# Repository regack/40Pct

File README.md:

The SmallFry 40% Board
=====

## v0.8-v0.10
* I forget everything that I did, lots of little things
* fixed some unconnected pads (oops)
* cleaned up silkscreens again
* fixed diode pads to fit SOD-123 footprint
* fixed BOM info for components
* rounded PCB edges
* replaced slotted holes with... holes
* added Vcc and Gnd pins to LED expansion
* changed LED expansion pins to 2.54 pitch

## v0.7 - 2013.10.20
* cleaned up silkscreens
* moved 'ROW5' expansion to GPIO7 (still ATMEGA32U4 pin8/PB0)
* added notes
* cleaned up and removed extra libs/mods

## v0.6 - 2013.10.16
* pulled extra pin for ROW5 from ATMEGA pin 8/PB0
* changed drills for holes/slots to work with OSHpark 
* added GPIO4, GPIO5, GPIO6 connectors to ATMEGA pins 26/PD6, 22/PD5, 11/PB3
* ran row and GPIO to 1.27mm headers on right-side of board for interconnect (ribbon cable spacing)

## v0.5 - 2013.09.20
* added back missing slot on right side of board
* added LEDs for optional keys from v0.4
* generated pcb image * not sure why slots don't render properly
* removed bottom-of-board expansion pins

## v0.4 - 2013.09.19
* added optional 1.25+1.0 and 1.0+1.25 for right-shift/fn keys

## v0.3 - 2013.09.18
* based on the GH60 Rev B PCB
* SMT ATMEGA32U4 and other components on back of board
* Expansion ports on bottom and top row
* LEDs on ESC, 'CAPS', and WASD Cluster
* Other LEDs in matrix with expansion points on top row

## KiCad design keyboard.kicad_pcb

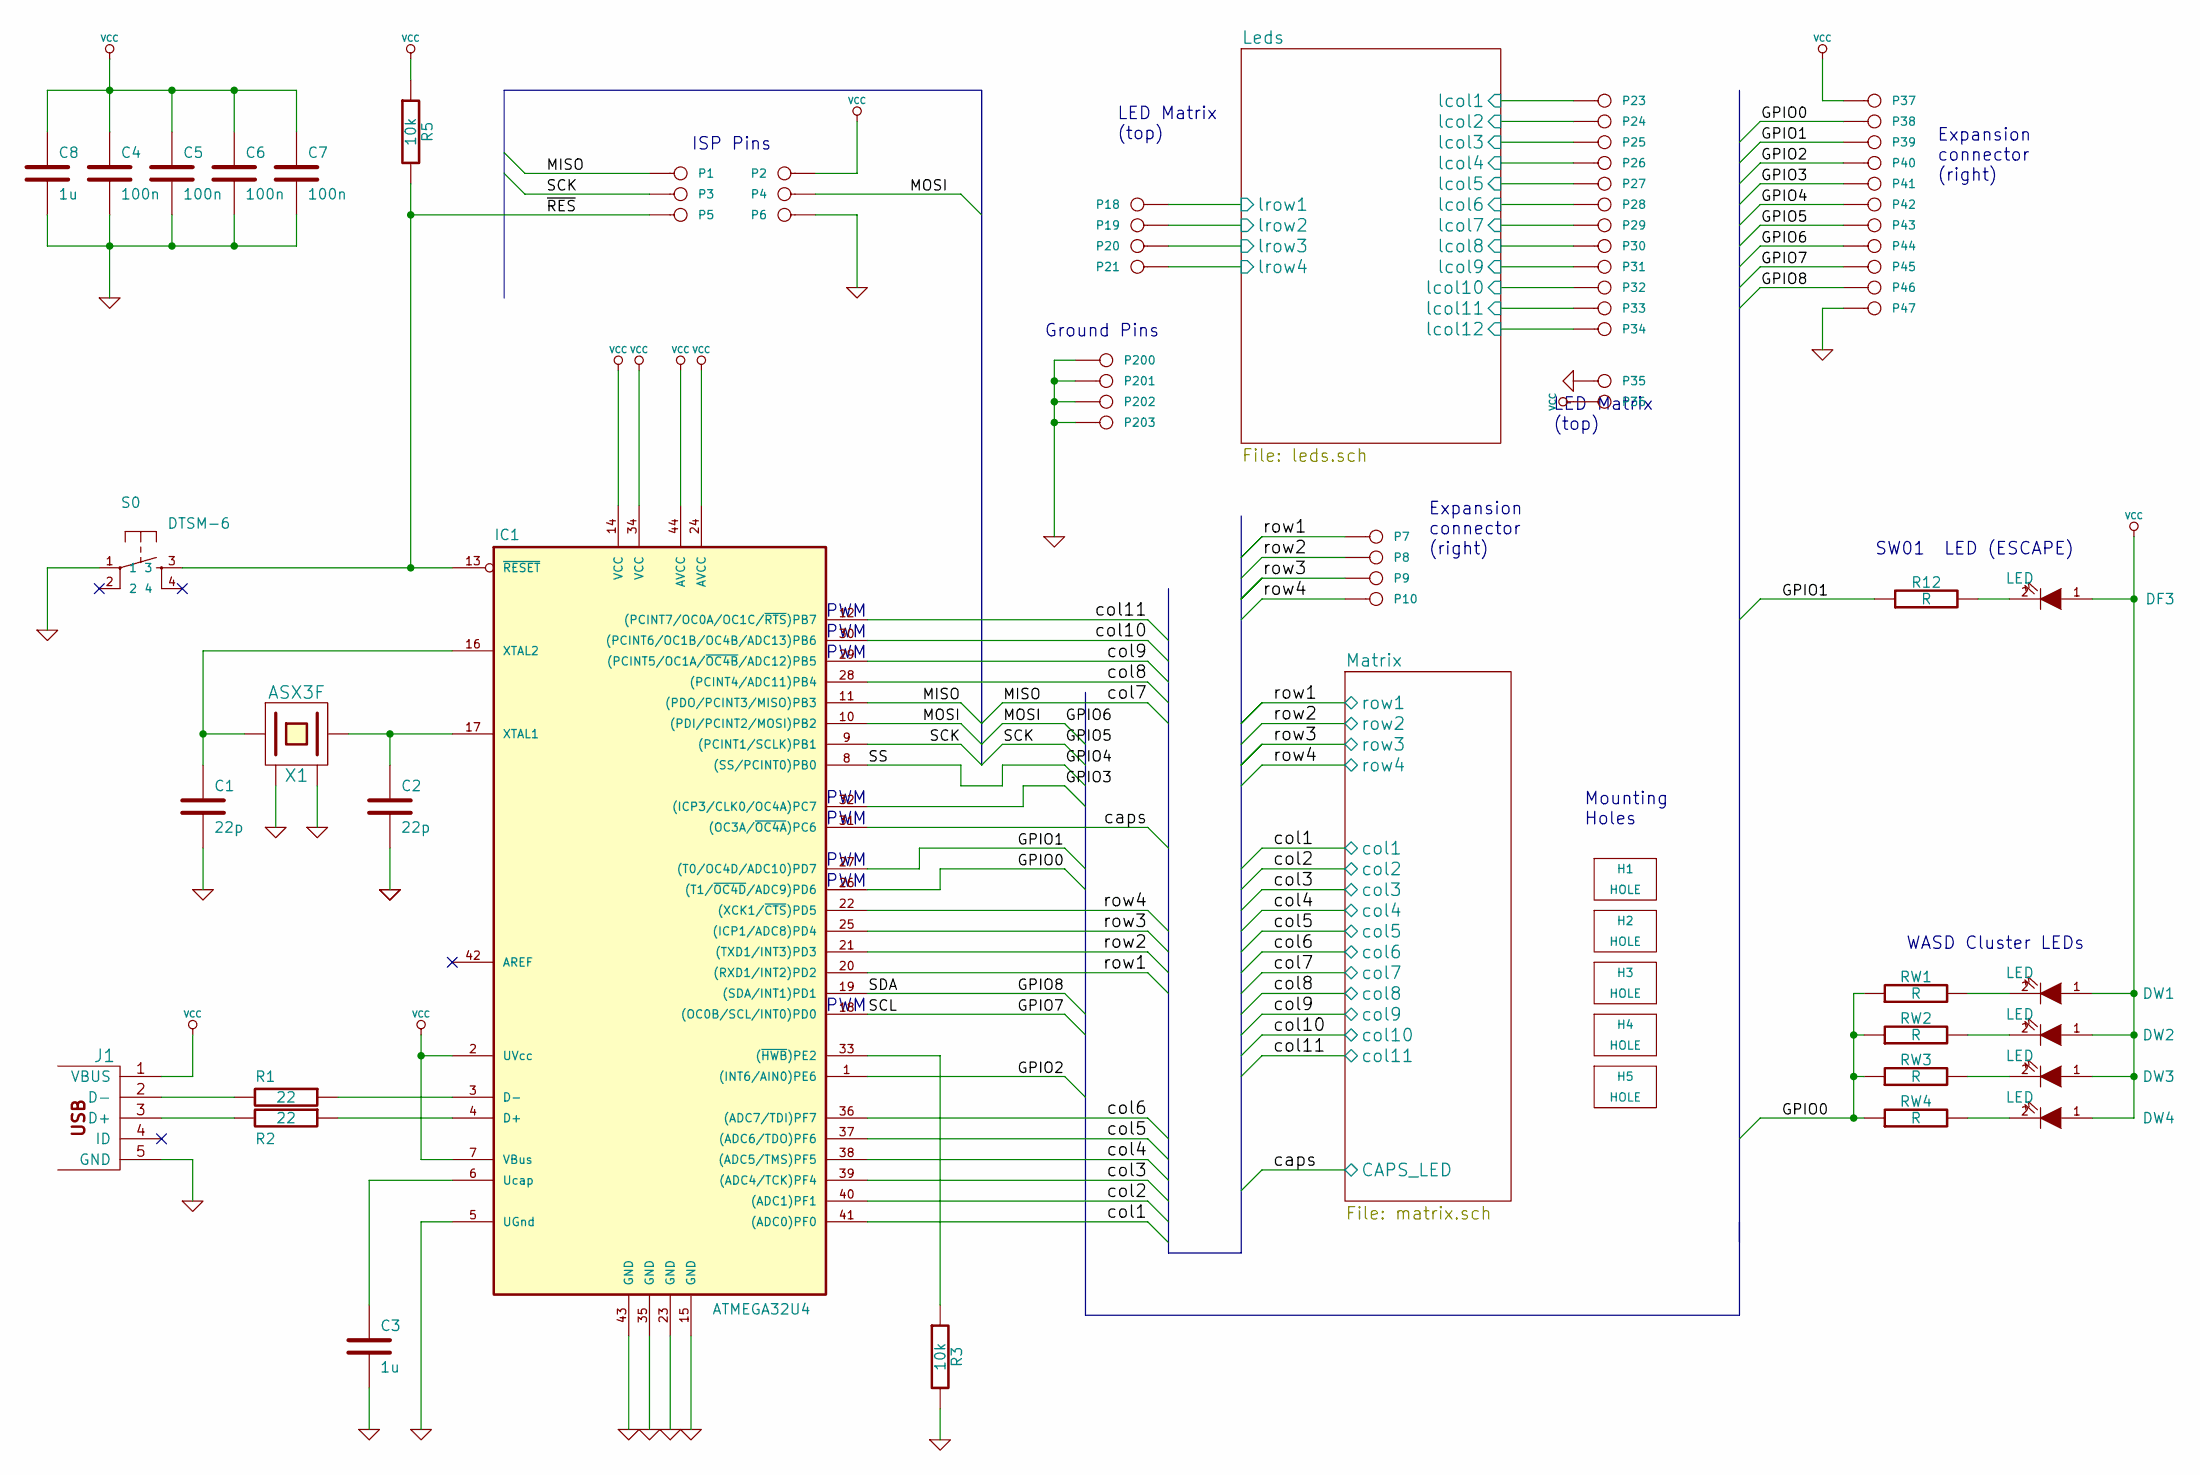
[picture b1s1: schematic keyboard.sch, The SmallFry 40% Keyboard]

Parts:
C1, C2: 22p
C3, C8: 1u
C4, C5, C6, C7: 100n
DF3: LED
DW1, DW2, DW3, DW4: LED
H1, H2, H3, H4, H5: HOLE
IC1: ATMEGA32U4; TQFP44
J1: MINI
P1: MISO
P2, P37: Vcc
P3: SCK
P4: MOSI
P5: RES
P6, P47, P200, P201, P202, P203: GND
P7: ROW1
P8: ROW2
P9: ROW3
P10: ROW4
P18: LR1
P19: LR2
P20: LR3
P21: LR4
P23: LC1
P24: LC2
P25: LC3
P26: LC4
P27: LC5
P28: LC6
P29: LC7
P30: LC8
P31: LC9
P32: LC10
P33: LC11
P34: LC12
P35: LGND
P36: LVcc
P38: GPIO0
P39: GPIO1
P40: GPIO2
P41: GPIO3
P42: GPIO4(SS)
P43: GPIO5(SCK)
P44: GPIO6(MOSI)
P45: GPIO7(SCL)
P46: GPIO8(SDA)
R1, R2: 22
R3, R5: 10k
R12: R
RW1, RW2, RW3, RW4: R
S0: DTSM-6; switch-tact-DTSM-6
X1: ASX3F

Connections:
/GPIO0: IC1.26 ((T1/~OC4D~/ADC9)PD6), P38.1, RW1.1, RW2.1, RW3.1, RW4.1
/GPIO1: IC1.27 ((T0/OC4D/ADC10)PD7), P39.1, R12.1
/GPIO2: IC1.1 ((INT6/AIN0)PE6), P40.1
/GPIO3: IC1.32 ((ICP3/CLK0/OC4A)PC7), P41.1
/GPIO4: IC1.8 ((SS/PCINT0)PB0), P42.1
/GPIO5: IC1.9 ((PCINT1/SCLK)PB1), P3.1, P43.1
/GPIO6: IC1.10 ((PDI/PCINT2/MOSI)PB2), P4.1, P44.1
/GPIO7: IC1.18 ((OC0B/SCL/INT0)PD0), P45.1
/GPIO8: IC1.19 ((SDA/INT1)PD1), P46.1
/Leds/lcol1: P23.1; also elsewhere on the board
/Leds/lcol2: P24.1; also elsewhere on the board
/Leds/lcol3: P25.1; also elsewhere on the board
/Leds/lcol4: P26.1; also elsewhere on the board
/Leds/lcol5: P27.1; also elsewhere on the board
/Leds/lcol6: P28.1; also elsewhere on the board
/Leds/lcol7: P29.1; also elsewhere on the board
/Leds/lcol8: P30.1; also elsewhere on the board
/Leds/lcol9: P31.1; also elsewhere on the board
/Leds/lcol10: P32.1; also elsewhere on the board
/Leds/lcol11: P33.1; also elsewhere on the board
/Leds/lcol12: P34.1; also elsewhere on the board
/Leds/lrow1: P18.1; also elsewhere on the board
/Leds/lrow2: P19.1; also elsewhere on the board
/Leds/lrow3: P20.1; also elsewhere on the board
/Leds/lrow4: P21.1; also elsewhere on the board
/Matrix/CAPS_LED: IC1.31 ((OC3A/~OC4A~)PC6); also elsewhere on the board
/Matrix/col1: IC1.41 ((ADC0)PF0); also elsewhere on the board
/Matrix/col2: IC1.40 ((ADC1)PF1); also elsewhere on the board
/Matrix/col3: IC1.39 ((ADC4/TCK)PF4); also elsewhere on the board
/Matrix/col4: IC1.38 ((ADC5/TMS)PF5); also elsewhere on the board
/Matrix/col5: IC1.37 ((ADC6/TDO)PF6); also elsewhere on the board
/Matrix/col6: IC1.36 ((ADC7/TDI)PF7); also elsewhere on the board
/Matrix/col7: IC1.11 ((PDO/PCINT3/MISO)PB3), P1.1; also elsewhere on the board
/Matrix/col8: IC1.28 ((PCINT4/ADC11)PB4); also elsewhere on the board
/Matrix/col9: IC1.29 ((PCINT5/OC1A/~OC4B~/ADC12)PB5); also elsewhere on the board
/Matrix/col10: IC1.30 ((PCINT6/OC1B/OC4B/ADC13)PB6); also elsewhere on the board
/Matrix/col11: IC1.12 ((PCINT7/OC0A/OC1C/~RTS~)PB7); also elsewhere on the board
/Matrix/row1: IC1.20 ((RXD1/INT2)PD2), P7.1; also elsewhere on the board
/Matrix/row2: IC1.21 ((TXD1/INT3)PD3), P8.1; also elsewhere on the board
/Matrix/row3: IC1.25 ((ICP1/ADC8)PD4), P9.1; also elsewhere on the board
/Matrix/row4: IC1.22 ((XCK1/~CTS~)PD5), P10.1; also elsewhere on the board
/~RES~: IC1.13 (~RESET~), P5.1, R5.2, S0.3
GND: C1.2, C2.2, C3.2, C4.2, C5.2, C6.2, C7.2, C8.2, IC1.5 (UGnd), IC1.15 (GND), IC1.23 (GND), IC1.35 (GND), IC1.43 (GND), J1.5 (GND), P6.1, P35.1, P47.1, P200.1, P201.1, P202.1, P203.1, R3.2, S0.1, X1.2 (GND), X1.4 (GND)
unnamed: C2.1, IC1.17 (XTAL1), X1.3 (2)
unnamed: C1.1, IC1.16 (XTAL2), X1.1
unnamed: J1.2 (D-), R1.2
unnamed: J1.3 (D+), R2.2
unnamed: C3.1, IC1.6 (Ucap)
unnamed: IC1.4 (D+), R2.1
unnamed: IC1.3 (D-), R1.1
unnamed: DW1.2 (K), RW1.2
unnamed: DW2.2 (K), RW2.2
unnamed: DW3.2 (K), RW3.2
unnamed: IC1.33 ((~HWB~)PE2), R3.1
unnamed: DF3.2 (K), R12.2
unnamed: DW4.2 (K), RW4.2
VCC: C4.1, C5.1, C6.1, C7.1, C8.1, DF3.1 (A), DW1.1 (A), DW2.1 (A), DW3.1 (A), DW4.1 (A), IC1.2 (UVcc), IC1.7 (VBus), IC1.14 (VCC), IC1.24 (AVCC), IC1.34 (VCC), IC1.44 (AVCC), J1.1 (VBUS), P2.1, P36.1, P37.1, R5.1; also elsewhere on the board

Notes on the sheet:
Expansion connector (right)
PWM
LED Matrix (top)
Mounting Holes
Ground Pins
ISP Pins
WASD Cluster LEDs
SW01 LED (ESCAPE)

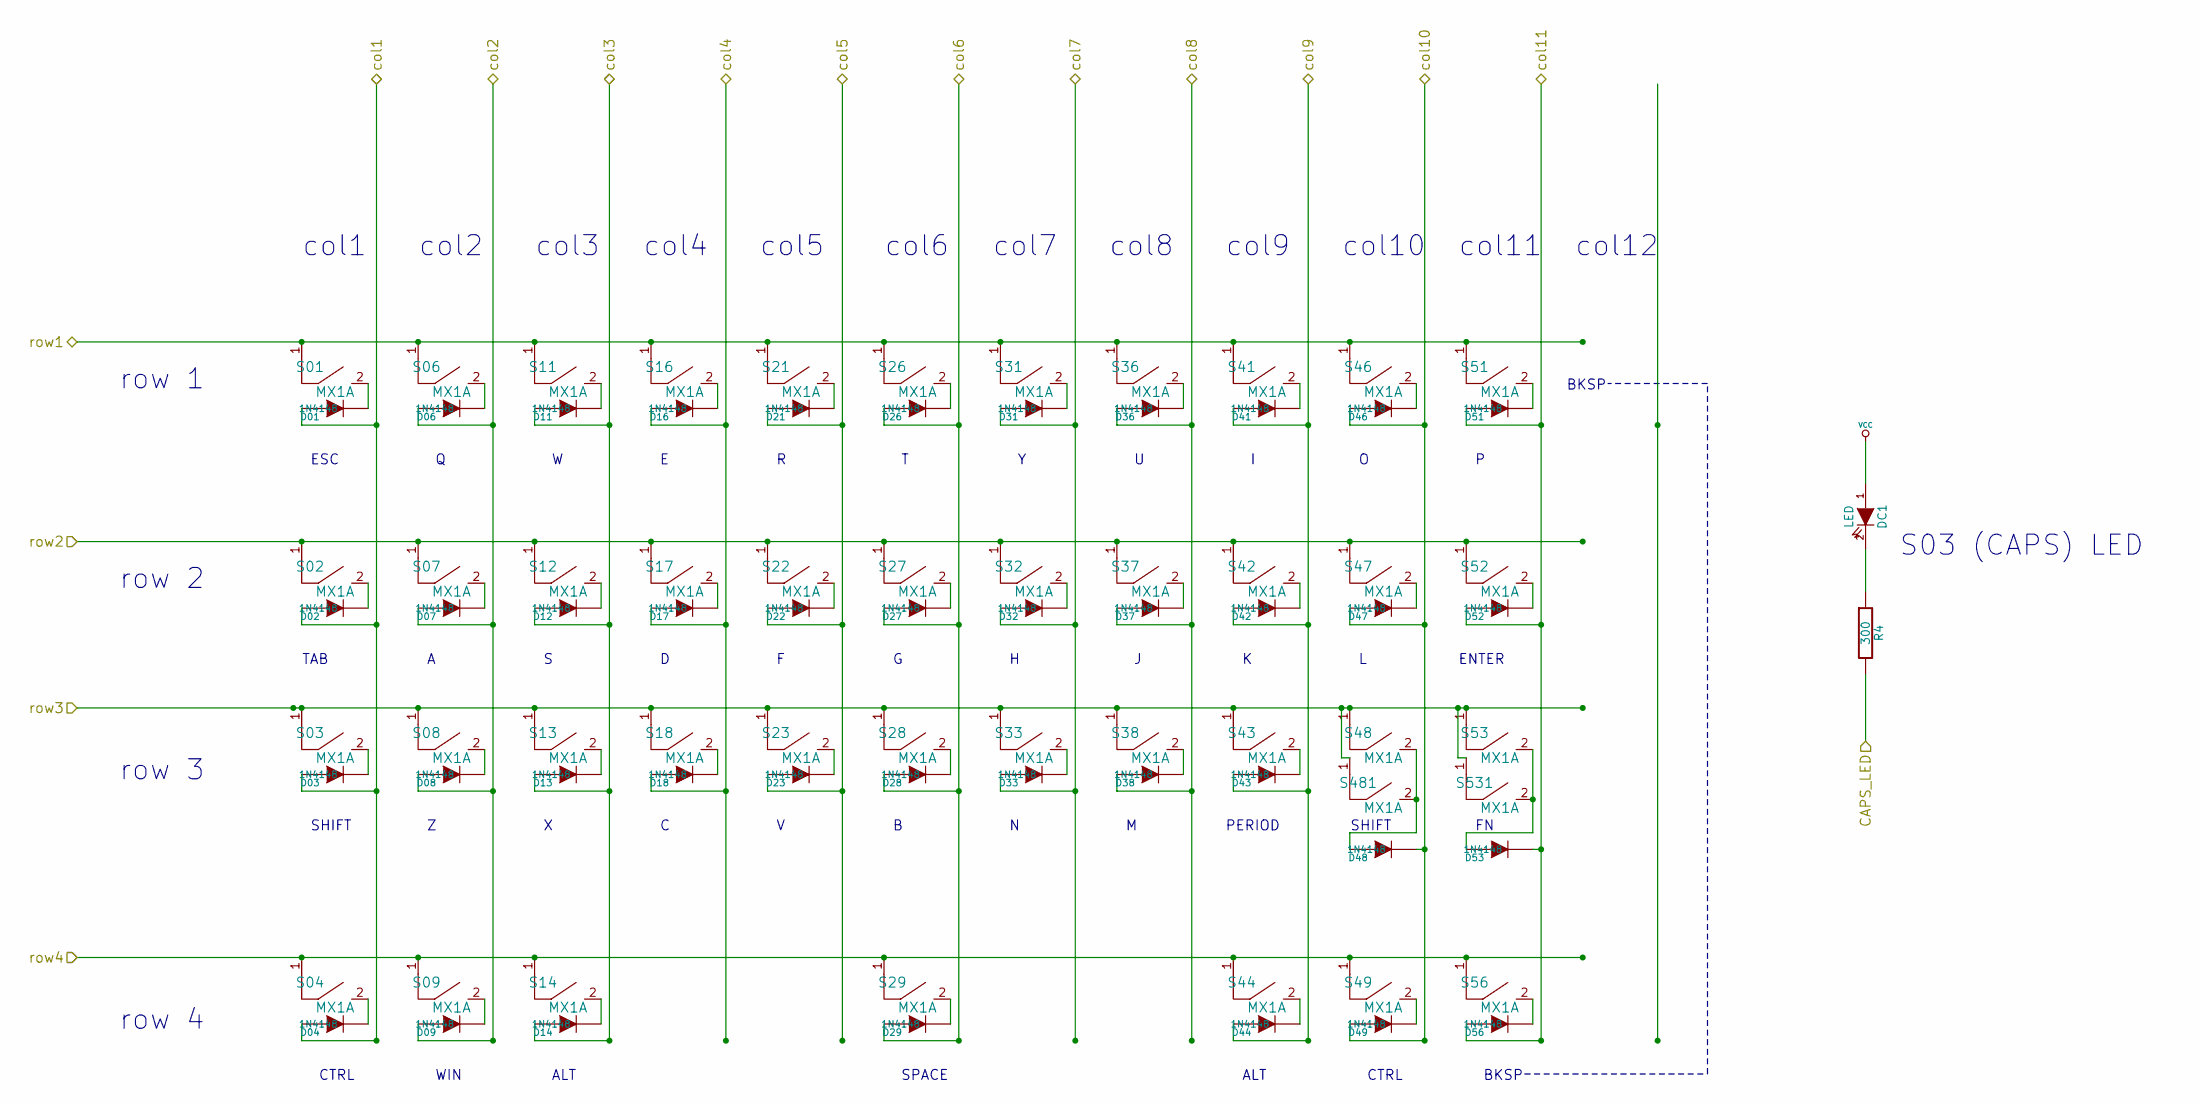
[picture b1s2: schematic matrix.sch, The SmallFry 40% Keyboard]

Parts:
D01, D02, D03, D04, D06, D07, D08, D09, D11, D12, D13, D14, D16, D17, D18, D21, D22, D23, D26, D27, D28, D29, D31, D32, D33, D36, D37, D38, D41, D42, D43, D44, D46, D47, D48, D49, D51, D52, D53, D56: 1N4148
DC1: LED
R4: 300
S01, S02, S03, S04, S06, S07, S08, S09, S11, S12, S13, S14, S16, S17, S18, S21, S22, S23, S26, S27, S28, S29, S31, S32, S33, S36, S37, S38, S41, S42, S43, S44, S46, S47, S48, S49, S51, S52, S53, S56, S481, S531: MX1A

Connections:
/Matrix/CAPS_LED: R4.2; also elsewhere on the board
/Matrix/col1: D01.1 (A), D02.1 (A), D03.1 (A), D04.1 (A); also elsewhere on the board
/Matrix/col2: D06.1 (A), D07.1 (A), D08.1 (A), D09.1 (A); also elsewhere on the board
/Matrix/col3: D11.1 (A), D12.1 (A), D13.1 (A), D14.1 (A); also elsewhere on the board
/Matrix/col4: D16.1 (A), D17.1 (A), D18.1 (A); also elsewhere on the board
/Matrix/col5: D21.1 (A), D22.1 (A), D23.1 (A); also elsewhere on the board
/Matrix/col6: D26.1 (A), D27.1 (A), D28.1 (A), D29.1 (A); also elsewhere on the board
/Matrix/col7: D31.1 (A), D32.1 (A), D33.1 (A); also elsewhere on the board
/Matrix/col8: D36.1 (A), D37.1 (A), D38.1 (A); also elsewhere on the board
/Matrix/col9: D41.1 (A), D42.1 (A), D43.1 (A), D44.1 (A); also elsewhere on the board
/Matrix/col10: D46.1 (A), D47.1 (A), D48.2 (K), D49.1 (A); also elsewhere on the board
/Matrix/col11: D51.1 (A), D52.1 (A), D53.2 (K), D56.1 (A); also elsewhere on the board
/Matrix/row1: S01.1, S06.1, S11.1, S16.1, S21.1, S26.1, S31.1, S36.1, S41.1, S46.1, S51.1; also elsewhere on the board
/Matrix/row2: S02.1, S07.1, S12.1, S17.1, S22.1, S27.1, S32.1, S37.1, S42.1, S47.1, S52.1; also elsewhere on the board
/Matrix/row3: S03.1, S08.1, S13.1, S18.1, S23.1, S28.1, S33.1, S38.1, S43.1, S48.1, S53.1, S481.1, S531.1; also elsewhere on the board
/Matrix/row4: S04.1, S09.1, S14.1, S29.1, S44.1, S49.1, S56.1; also elsewhere on the board
unnamed: D23.2 (K), S23.2
unnamed: D01.2 (K), S01.2
unnamed: D33.2 (K), S33.2
unnamed: D32.2 (K), S32.2
unnamed: D31.2 (K), S31.2
unnamed: D21.2 (K), S21.2
unnamed: D22.2 (K), S22.2
unnamed: D11.2 (K), S11.2
unnamed: D47.2 (K), S47.2
unnamed: D46.2 (K), S46.2
unnamed: D42.2 (K), S42.2
unnamed: D43.2 (K), S43.2
unnamed: D38.2 (K), S38.2
unnamed: D37.2 (K), S37.2
unnamed: D41.2 (K), S41.2
unnamed: D36.2 (K), S36.2
unnamed: D12.2 (K), S12.2
unnamed: D26.2 (K), S26.2
unnamed: D14.2 (K), S14.2
unnamed: D09.2 (K), S09.2
unnamed: D13.2 (K), S13.2
unnamed: D08.2 (K), S08.2
unnamed: D07.2 (K), S07.2
unnamed: D02.2 (K), S02.2
unnamed: D17.2 (K), S17.2
unnamed: D18.2 (K), S18.2
unnamed: D16.2 (K), S16.2
unnamed: D29.2 (K), S29.2
unnamed: D28.2 (K), S28.2
unnamed: D27.2 (K), S27.2
unnamed: D03.2 (K), S03.2
unnamed: D48.1 (A), S48.2, S481.2
unnamed: D53.1 (A), S53.2, S531.2
unnamed: D04.2 (K), S04.2
unnamed: D56.2 (K), S56.2
unnamed: D49.2 (K), S49.2
unnamed: D44.2 (K), S44.2
unnamed: D52.2 (K), S52.2
unnamed: D51.2 (K), S51.2
unnamed: DC1.2 (K), R4.1
unnamed: D06.2 (K), S06.2
VCC: DC1.1 (A); also elsewhere on the board

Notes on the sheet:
row 1
row 2
row 3
row 4
col1
col2
col3
col4
col5
col6
col7
col9
col10
col11
col12
col8
ESC
TAB
BKSP
SHIFT
ENTER
CTRL
WIN
ALT
PERIOD
SPACE
S03 (CAPS) LED

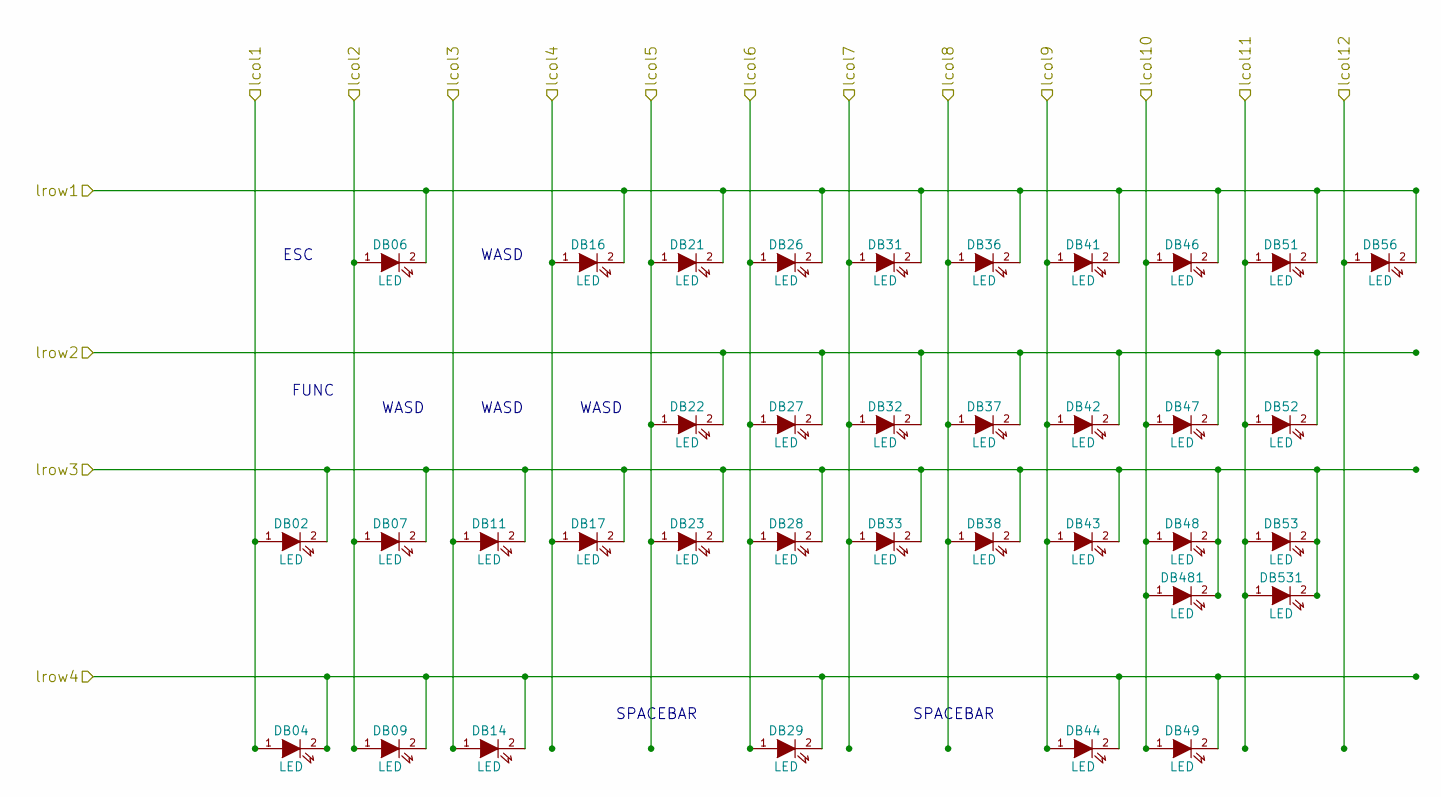
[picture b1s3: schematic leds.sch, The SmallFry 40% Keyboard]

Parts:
DB02, DB04, DB06, DB07, DB09, DB11, DB14, DB16, DB17, DB21, DB22, DB23, DB26, DB27, DB28, DB29, DB31, DB32, DB33, DB36, DB37, DB38, DB41, DB42, DB43, DB44, DB46, DB47, DB48, DB49, DB51, DB52, DB53, DB56, DB481, DB531: LED

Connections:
/Leds/lcol1: DB02.1 (A), DB04.1 (A); also elsewhere on the board
/Leds/lcol2: DB06.1 (A), DB07.1 (A), DB09.1 (A); also elsewhere on the board
/Leds/lcol3: DB11.1 (A), DB14.1 (A); also elsewhere on the board
/Leds/lcol4: DB16.1 (A), DB17.1 (A); also elsewhere on the board
/Leds/lcol5: DB21.1 (A), DB22.1 (A), DB23.1 (A); also elsewhere on the board
/Leds/lcol6: DB26.1 (A), DB27.1 (A), DB28.1 (A), DB29.1 (A); also elsewhere on the board
/Leds/lcol7: DB31.1 (A), DB32.1 (A), DB33.1 (A); also elsewhere on the board
/Leds/lcol8: DB36.1 (A), DB37.1 (A), DB38.1 (A); also elsewhere on the board
/Leds/lcol9: DB41.1 (A), DB42.1 (A), DB43.1 (A), DB44.1 (A); also elsewhere on the board
/Leds/lcol10: DB46.1 (A), DB47.1 (A), DB48.1 (A), DB49.1 (A), DB481.1 (A); also elsewhere on the board
/Leds/lcol11: DB51.1 (A), DB52.1 (A), DB53.1 (A), DB531.1 (A); also elsewhere on the board
/Leds/lcol12: DB56.1 (A); also elsewhere on the board
/Leds/lrow1: DB06.2 (K), DB16.2 (K), DB21.2 (K), DB26.2 (K), DB31.2 (K), DB36.2 (K), DB41.2 (K), DB46.2 (K), DB51.2 (K), DB56.2 (K); also elsewhere on the board
/Leds/lrow2: DB22.2 (K), DB27.2 (K), DB32.2 (K), DB37.2 (K), DB42.2 (K), DB47.2 (K), DB52.2 (K); also elsewhere on the board
/Leds/lrow3: DB02.2 (K), DB07.2 (K), DB11.2 (K), DB17.2 (K), DB23.2 (K), DB28.2 (K), DB33.2 (K), DB38.2 (K), DB43.2 (K), DB48.2 (K), DB53.2 (K), DB481.2 (K), DB531.2 (K); also elsewhere on the board
/Leds/lrow4: DB04.2 (K), DB09.2 (K), DB14.2 (K), DB29.2 (K), DB44.2 (K), DB49.2 (K); also elsewhere on the board

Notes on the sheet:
WASD
FUNC
ESC
SPACEBAR

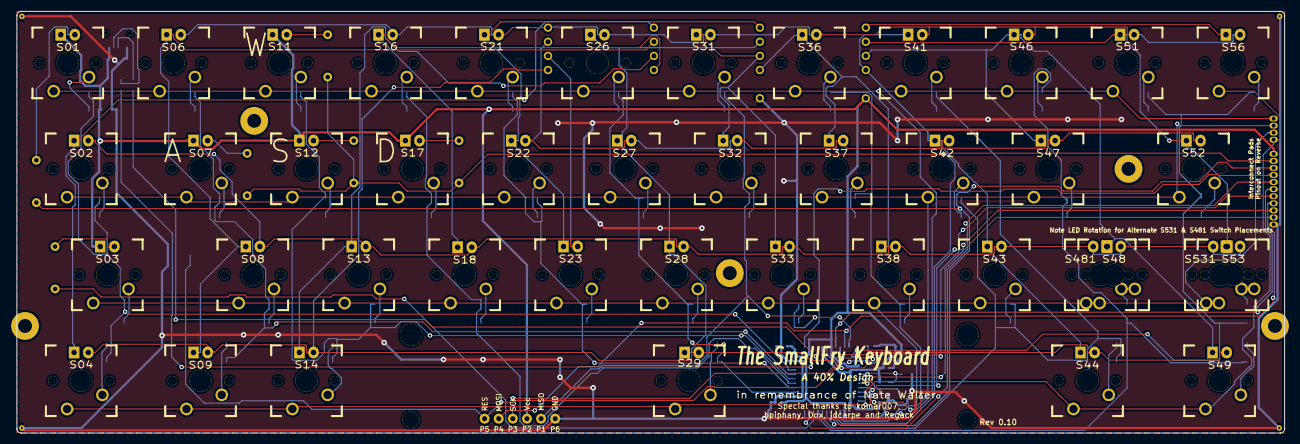
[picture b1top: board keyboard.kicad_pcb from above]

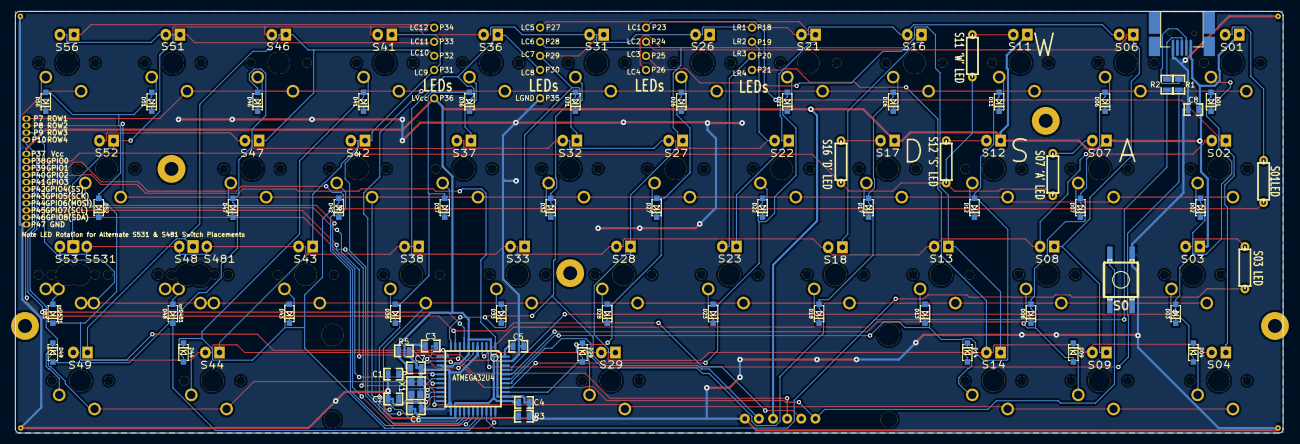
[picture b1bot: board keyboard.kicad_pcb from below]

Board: 2 copper layers, 228.0 x 75.8 mm, 194 parts (97 on the bottom side), 98 nets.

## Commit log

2013-03-06 v1.3
2013-03-06 Fixed formatting
2013-03-06 screenshot
2013-03-07 v1.4
2013-03-07 v1.4 removed old files
2013-09-18 Updating to new layout
2013-09-18 v0.3
2013-09-18 Forked for regack
2013-09-18 v0.3.8
2013-09-20 v0.4
2013-09-20 v0.5
2013-10-16 v0.6
2013-10-16 Typo
2013-10-20 v0.7
2013-11-26 v0.10
2013-11-26 cleanup
